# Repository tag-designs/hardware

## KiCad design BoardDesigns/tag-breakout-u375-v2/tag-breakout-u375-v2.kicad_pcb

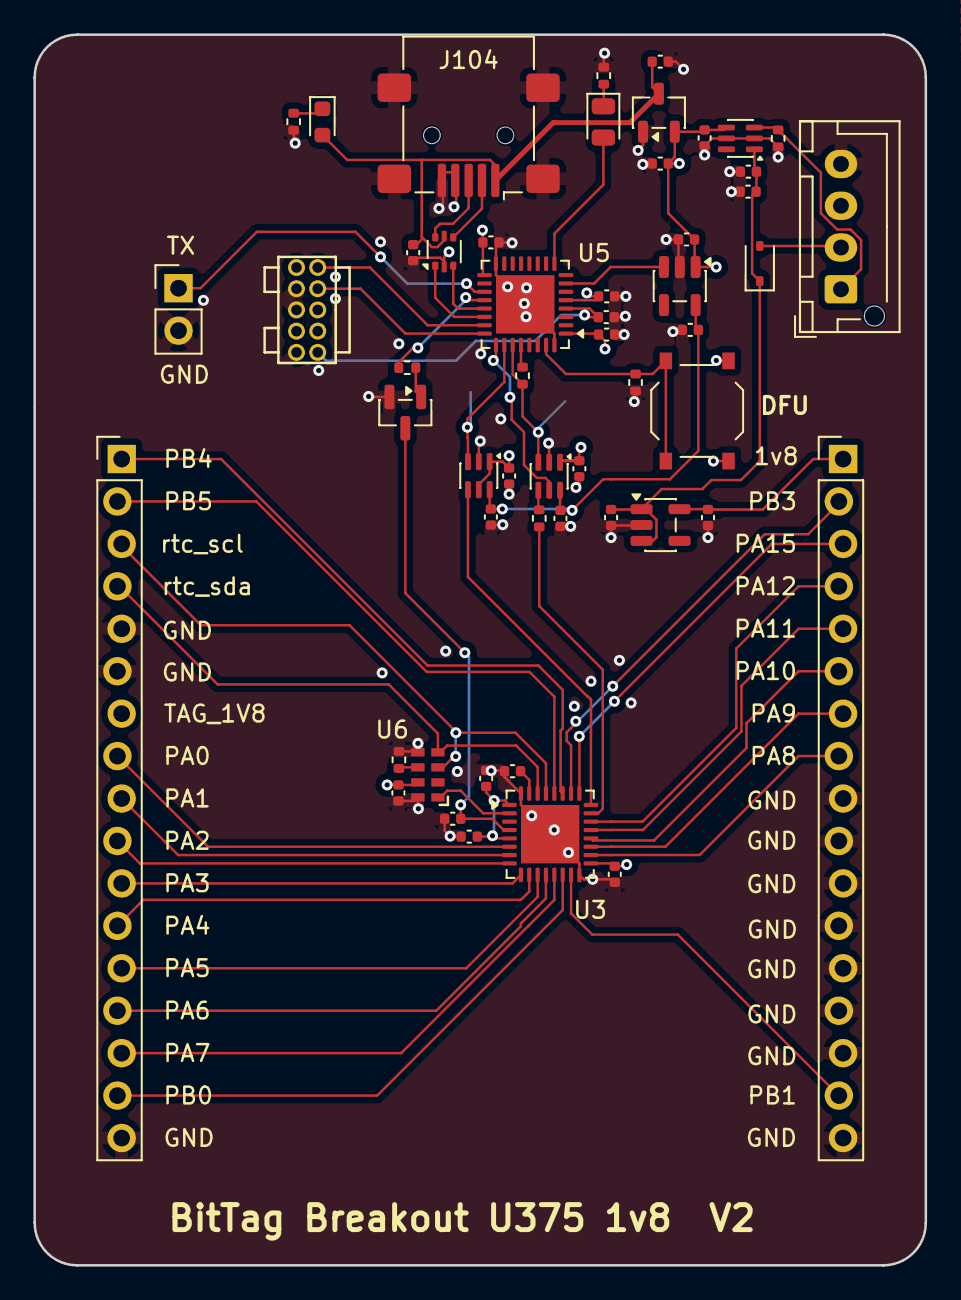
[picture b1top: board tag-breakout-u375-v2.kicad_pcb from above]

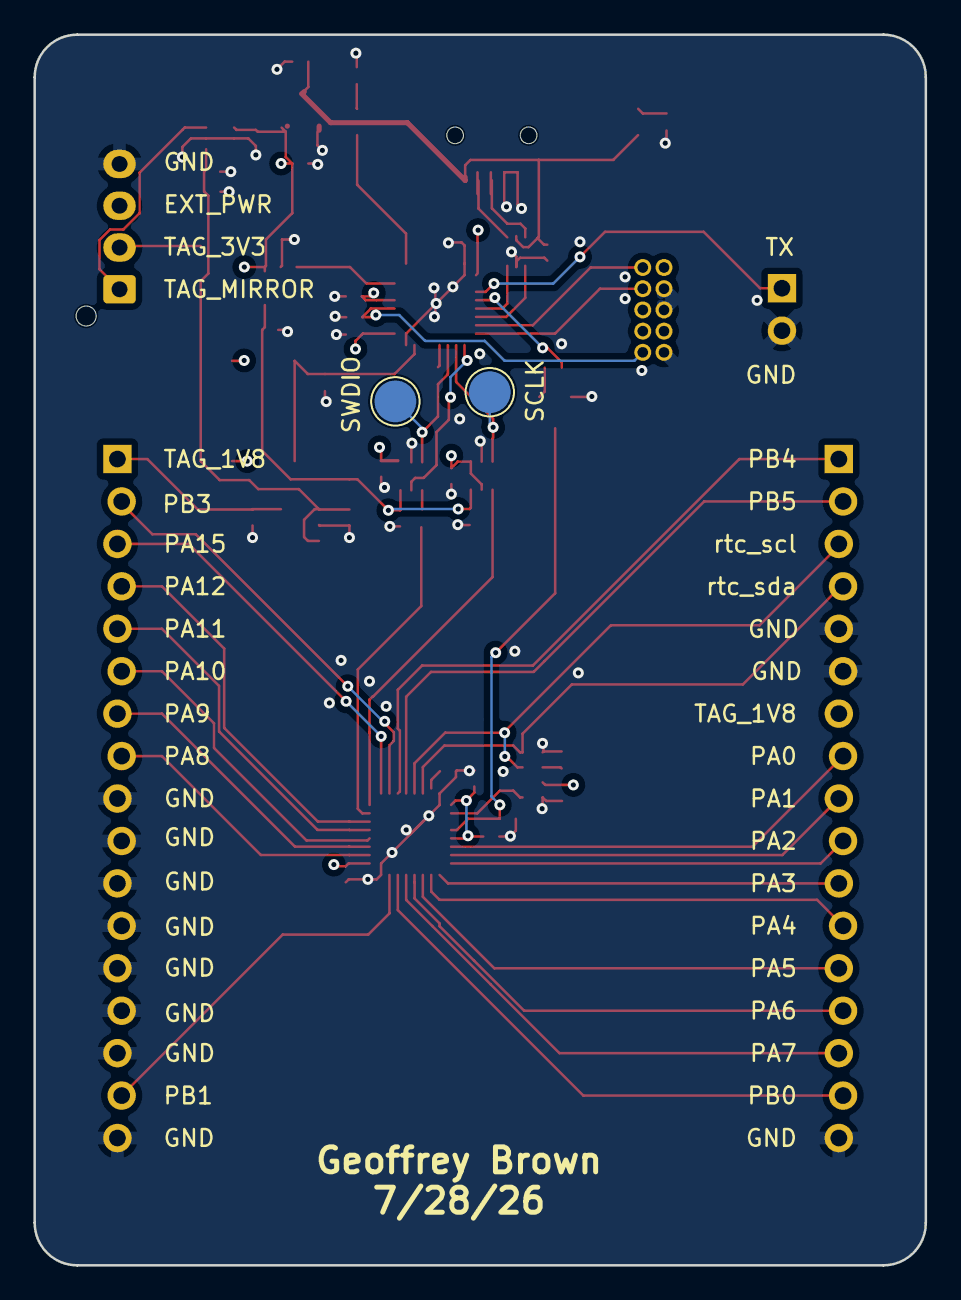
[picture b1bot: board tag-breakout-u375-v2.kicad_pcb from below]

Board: 4 copper layers, 53.3 x 73.7 mm, 55 parts (2 on the bottom side), 55 nets.

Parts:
C1, C12, C104, C105, C106, C108, C112, C114: 1uF; C_0402_1005Metric
C2, C3, C5, C6, C7, C9, C11, C101, C102, C103, C107, C109, C110, C111, C113: 0.1uF; C_0402_1005Metric
C8: 4.7uF; C_0402_1005Metric
D1: LED-GREEN; LED_0805_2012Metric
D4: D_Schottky; D_SOD-323
D105: LED-RED; LED_0603_1608Metric
J1: Conn_01x04_Female; JST_XH_B04B-XH-AM_1x04_P2.50mm_Vertical
J2: Conn_01x02_Male; PinHeader_1x02_P2.54mm_Vertical
J3, J4: Conn_01x17; PinHeader_1x17_P2.54mm_Vertical_Staggered
J102: Conn_02x05_Odd_Even; FTSH-105-01-F-D-K
J104: USB_B_Mini; USB_Mini-B_Lumberg_2486_01_Horizontal
Q1: Q_NPN_BEC; SOT-23
R1, R2, R106: 100; R_0402_1005Metric
R3, R7, R105: 12K; R_0402_1005Metric
R104: 2.2K; R_0402_1005Metric
R107: 200; R_0402_1005Metric
TP1, TP2: TestPoint; TestPoint_Pad_D2.5mm
U1: XC6206; SOT-23-3
U2: SiP32432DR3; SOT-363_SC-70-6
U3: stm32U375; UFQFPN-32-1EP_5x5mm_P0.5mm_EP3.5x3.5mm
U4: USBLC6-2P6; SOT-666
U5: stm32l432; UFQFPN-32-1EP_5x5mm_P0.5mm_EP3.5x3.5mm
U6: RV-3028-C7; RV-8803-C7
U7, U8: SN74LVC1T45DCK; SOT-363_SC-70-6
U10: AP2112K-1.8; SOT-23-5
U11: TPS7A0218PDBVR; SOT-23-5
U105: Tactile Switch; SW_SPST_TS_1187

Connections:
+1V8: C103.1, C105.1, C109.1, U7.6 (VCCB), U8.6 (VCCB), U10.5 (VOUT)
+3V3: C2.1, C11.1, C12.1, C104.1, C107.1, C110.1, C111.1, C112.1, J102.1, U1.2 (VO), U2.4 (IN), U5.1 (VDD), U5.5 (VDDA/VREF+), U5.17 (VDD), U7.1 (VCCA), U7.5 (DIR), U8.1 (VCCA), U10.1 (VIN), U105.2 (B)
/DM: J104.2 (D-), U4.4 (I/O2)
/DP: J104.3 (D+), U4.6 (I/O1)
/LED_GREEN: D1.2 (A), U5.9 (PA3)
/NRST: C101.1, J102.10, U5.4 (~NRST)
/SCLK: J102.4, U5.24 (PA14)
/SWDIO: J102.2, U5.23 (PA13)
/UART_TX: J2.1, U5.19 (PA9)
/USB_DM: U4.3 (I/O2), U5.21 (PA11)
/USB_DP: U4.1 (I/O1), U5.22 (PA12)
/boot0: R105.2, U5.31 (BOOT0), U105.1 (A)
/en1.8v: U5.7 (PA1), U10.3 (EN)
/stm32/NRST: C5.1, Q1.3 (C), U3.4 (~NRST)
/stm32/PA0: J3.8, U3.6 (PA0)
/stm32/PA1: J3.9, U3.7 (PA1)
/stm32/PA2: J3.10, U3.8 (PA2)
/stm32/PA3: J3.11, U3.9 (PA3)
/stm32/PA4: J3.12, U3.10 (PA4)
/stm32/PA5: J3.13, U3.11 (PA5)
/stm32/PA6: J3.14, U3.12 (PA6)
/stm32/PA7: J3.15, U3.13 (PA7)
/stm32/PA8: J4.8, U3.18 (PA8)
/stm32/PA9: J4.7, U3.19 (PA9)
/stm32/PA10: J4.6, U3.20 (PA10)
/stm32/PA11: J4.5, U3.21 (PA11)
/stm32/PA12: J4.4, U3.22 (PA12)
/stm32/PA15: J4.3, U3.25 (PA15)
/stm32/PB0: J3.16, U3.14 (PB0)
/stm32/PB1: J4.16, U3.15 (PB1)
/stm32/PB3: J4.2, U3.26 (PB3)
/stm32/PB4: J3.1, U3.27 (PB4)
/stm32/PB5: J3.2, U3.28 (PB5)
/stm32/VBACK: R3.2, U6.6 (VBACK)
/stm32/clkout: U3.2 (PC14), U6.1 (CLKOUT)
/stm32/rtc_scl: J3.3, U3.29 (PB6), U6.3 (SCL)
/stm32/rtc_sda: J3.4, U3.30 (BOOT0-PB7), U6.4 (SDA)
GND: C1.2, C2.2, C3.2, C5.2, C6.2, C7.2, C8.2, C9.2, C11.2, C12.2, C101.2, C102.2, C103.2, C104.2, C105.2, C106.2, C107.2, C108.2, C109.2, C110.2, C111.2, C112.2, C113.2, C114.2, J1.4, J2.2, J3.5, J3.6, J3.17, J4.9, J4.10, J4.11, J4.12, J4.13, J4.14, J4.15, J4.17, J102.3, J102.5, J102.9, J104.4 (ID), J104.5 (GND), J104.SH (Shield), Q1.2 (E), R1.2, R3.1, R7.2, R105.1, R107.2, U1.1 (GND), U2.2 (GND), U2.5 (GND), U3.16 (VSS), U3.32 (VSS), U3.33 (GND), U4.2 (GND), U5.16 (VSS), U5.32 (VSS), U5.33 (GND), U6.5 (GND), U6.8 (EVI), U7.2 (GND), U8.2 (GND), U10.2 (GND), U11.2 (GND)
unnamed: D1.1 (K), R1.1
unnamed: D105.1 (K), R107.1
unnamed: C8.1, U3.31 (VCAP)
unnamed: R104.1, U5.20 (PA10)
unnamed: U5.25 (PA15), U8.5 (DIR)
unnamed: TP2.1 (1_1), U5.26 (PB3), U7.3 (A)
unnamed: R2.2, TP1.1 (1_1), U5.27 (PB4), U8.3 (A)
unnamed: R2.1, U5.28 (PB5)
unnamed: R106.1, U8.4 (B)
PWR_IN: D4.2 (A), J1.2
PWR_IN_MIRROR: J1.1, R7.1, U2.3 (~ON)
TAG_1V8: C3.1, C6.1, C7.1, C9.1, C106.1, J3.7, J4.1, U3.1 (VDD), U3.5 (VDDA/VREF+), U3.17 (VDD), U6.7 (VDD), U11.5 (OUT)
TAG_3V3: C108.1, C113.1, C114.1, D4.1 (K), U2.1 (OUT), U11.1 (IN), U11.3 (EN)
TAG_RESET: Q1.1 (B), R104.2
TAG_SCK: U3.24 (PA14), U7.4 (B)
TAG_SWDIO: R106.2, U3.23 (PA13)
VUSB: C1.1, C102.1, D105.2 (A), J104.1 (VBUS), U1.3 (VI), U4.5 (VBUS)

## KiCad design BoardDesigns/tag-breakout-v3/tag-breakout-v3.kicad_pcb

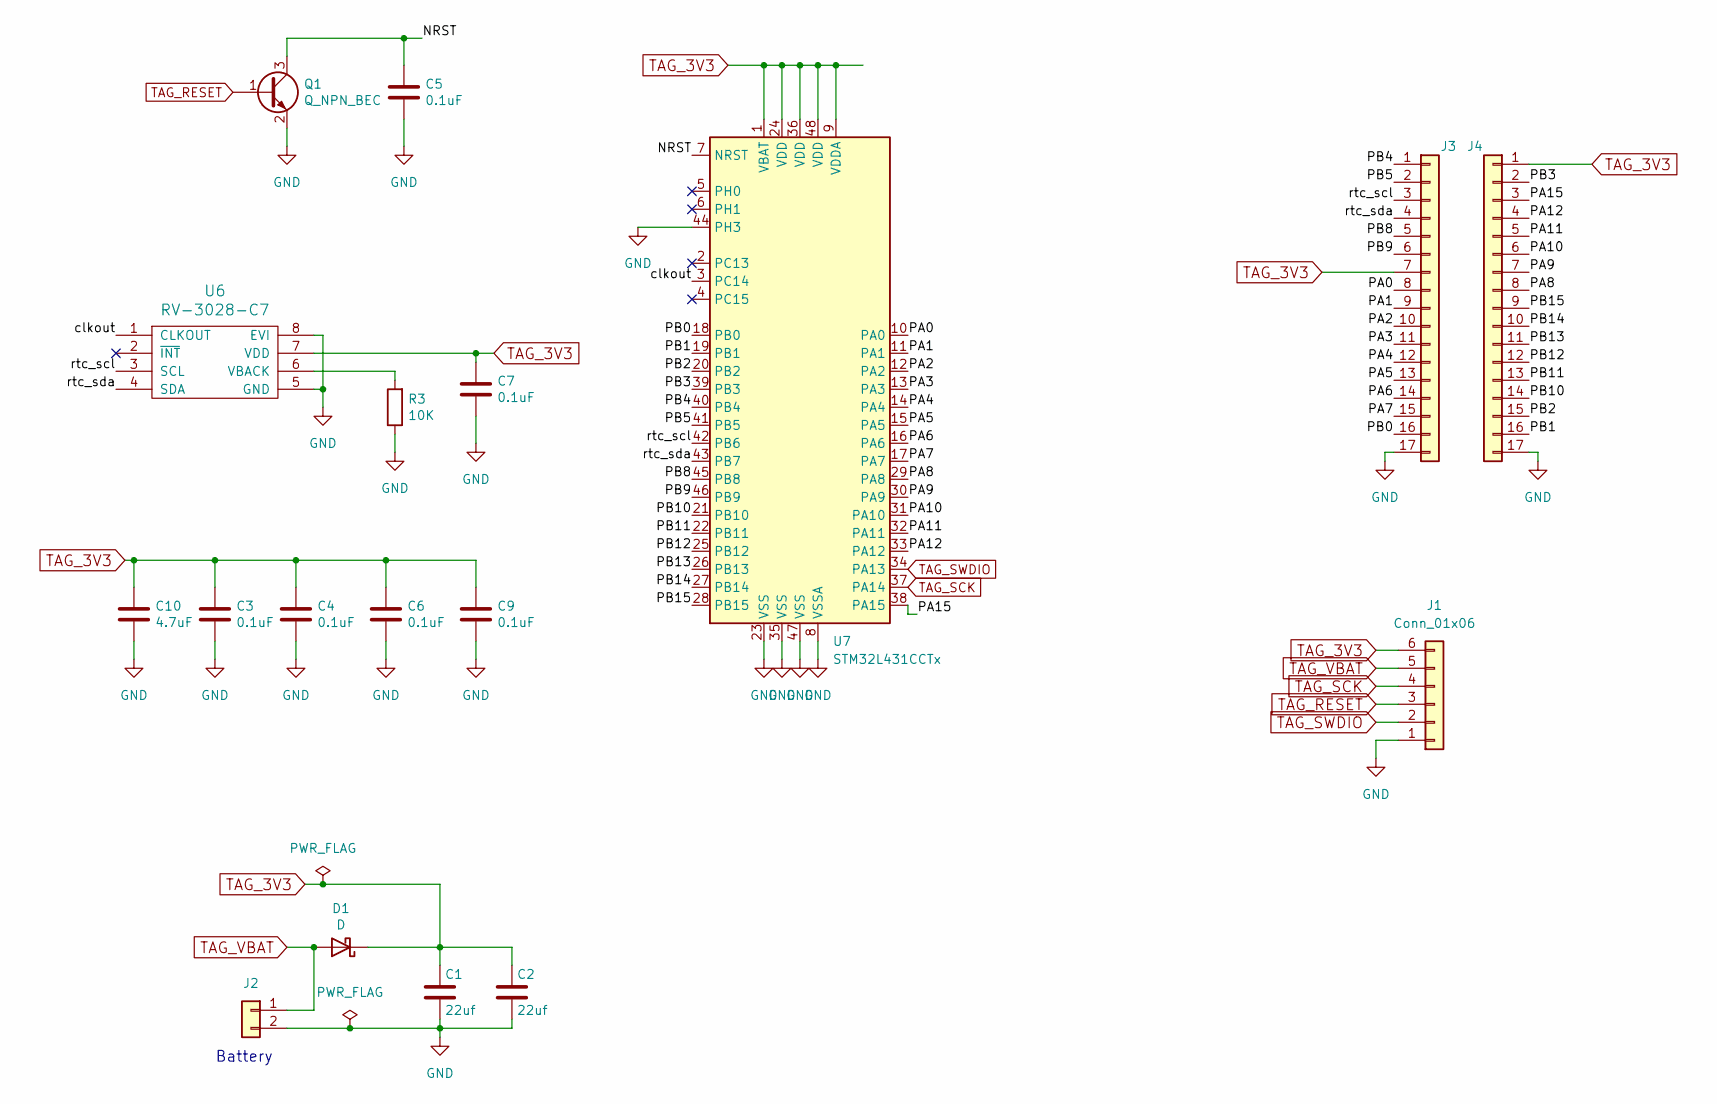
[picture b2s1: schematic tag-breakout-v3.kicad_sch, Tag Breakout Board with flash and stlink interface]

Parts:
C1, C2: 22uf; C_0402_1005Metric; MPN 04026D226MAT2A
C3, C4, C5, C6, C7, C9: 0.1uF; C_0603_1608Metric; LCSC C14663
C10: 4.7uF; C_0603_1608Metric; LCSC C19666
D1: D; D_0402_1005Metric; MPN CDBQC0130L-HF
J1: Conn_01x06; CONN_B6B-ZR_JST
J2: CONN_01X02; PinHeader_1x02_P2.54mm_Vertical
J3, J4: Conn_01x17; PinSocket_1x17_P2.54mm_Vertical
Q1: Q_NPN_BEC; SOT-23; LCSC C20527
R3: 10K; R_0603_1608Metric; LCSC C25804
U6: RV-3028-C7; RV-8803-C7
U7: STM32L431CCTx; LQFP-48_7x7mm_P0.5mm; JLC C486681

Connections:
/NRST: C5.1, Q1.3 (C), U7.7 (NRST)
/PA0: J3.8, U7.10 (PA0)
/PA1: J3.9, U7.11 (PA1)
/PA2: J3.10, U7.12 (PA2)
/PA3: J3.11, U7.13 (PA3)
/PA4: J3.12, U7.14 (PA4)
/PA5: J3.13, U7.15 (PA5)
/PA6: J3.14, U7.16 (PA6)
/PA7: J3.15, U7.17 (PA7)
/PA8: J4.8, U7.29 (PA8)
/PA9: J4.7, U7.30 (PA9)
/PA10: J4.6, U7.31 (PA10)
/PA11: J4.5, U7.32 (PA11)
/PA12: J4.4, U7.33 (PA12)
/PA15: J4.3, U7.38 (PA15)
/PB0: J3.16, U7.18 (PB0)
/PB1: J4.16, U7.19 (PB1)
/PB2: J4.15, U7.20 (PB2)
/PB3: J4.2, U7.39 (PB3)
/PB4: J3.1, U7.40 (PB4)
/PB5: J3.2, U7.41 (PB5)
/PB8: J3.5, U7.45 (PB8)
/PB9: J3.6, U7.46 (PB9)
/PB10: J4.14, U7.21 (PB10)
/PB11: J4.13, U7.22 (PB11)
/PB12: J4.12, U7.25 (PB12)
/PB13: J4.11, U7.26 (PB13)
/PB14: J4.10, U7.27 (PB14)
/PB15: J4.9, U7.28 (PB15)
/clkout: U6.1 (CLKOUT), U7.3 (PC14)
/rtc_scl: J3.3, U6.3 (SCL), U7.42 (PB6)
/rtc_sda: J3.4, U6.4 (SDA), U7.43 (PB7)
GND: C1.2, C2.2, C3.2, C4.2, C5.2, C6.2, C7.2, C9.2, C10.2, J1.1, J2.2, J3.17, J4.17, Q1.2 (E), R3.1, U6.5 (GND), U6.8 (EVI), U7.8 (VSSA), U7.23 (VSS), U7.35 (VSS), U7.44 (PH3), U7.47 (VSS)
unnamed: R3.2, U6.6 (VBACK)
TAG_3V3: C1.1, C2.1, C3.1, C4.1, C6.1, C7.1, C9.1, C10.1, D1.1 (K), J1.6, J3.7, J4.1, U6.7 (VDD), U7.1 (VBAT), U7.9 (VDDA), U7.24 (VDD), U7.36 (VDD), U7.48 (VDD)
TAG_RESET: J1.3, Q1.1 (B)
TAG_SCK: J1.4, U7.37 (PA14)
TAG_SWDIO: J1.2, U7.34 (PA13)
TAG_VBAT: D1.2 (A), J1.5, J2.1

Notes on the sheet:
Battery

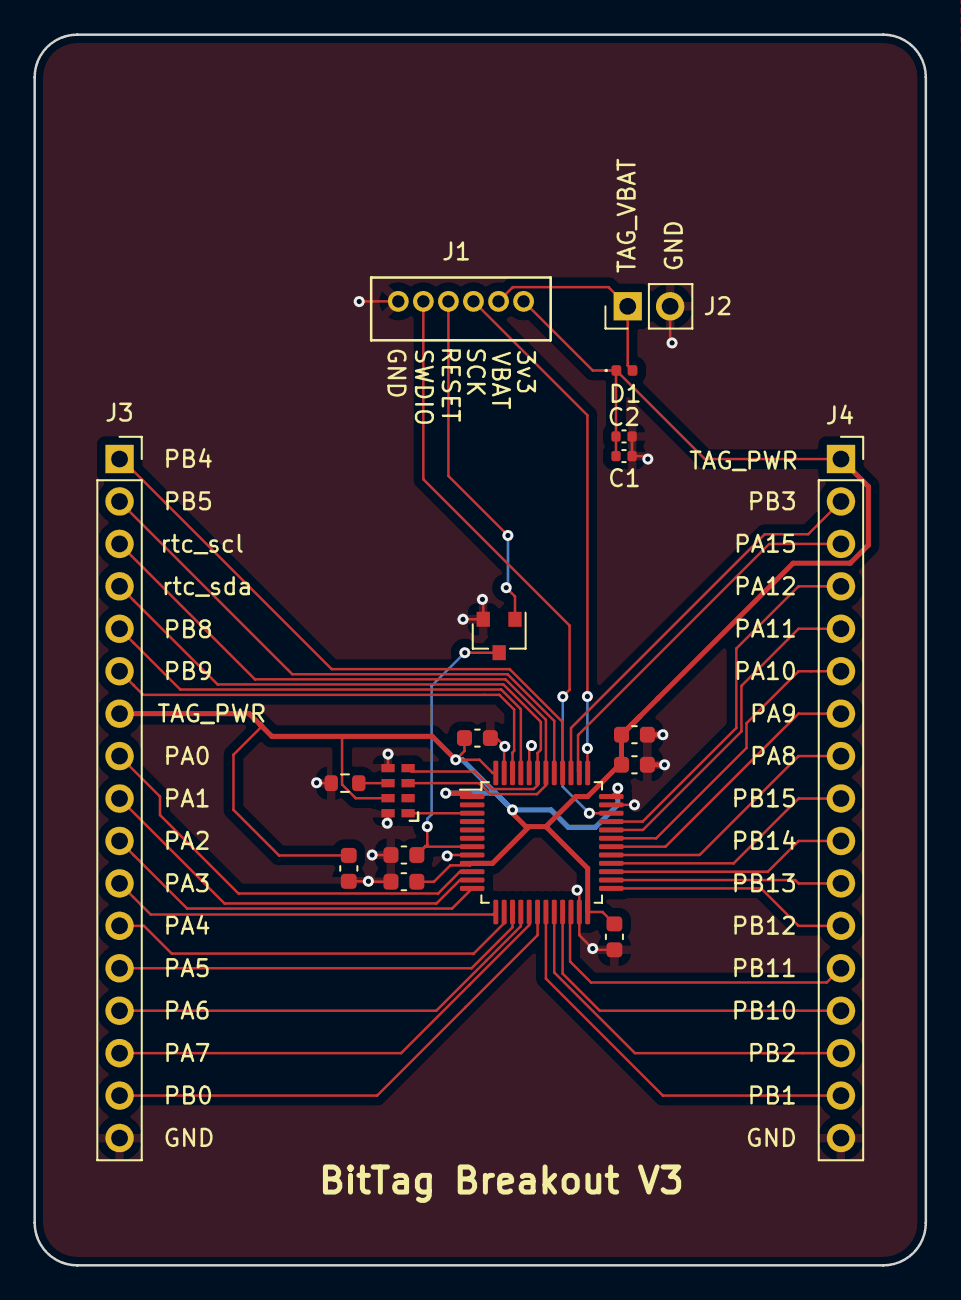
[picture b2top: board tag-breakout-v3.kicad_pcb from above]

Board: 2 copper layers, 53.3 x 73.7 mm, 18 parts (0 on the bottom side), 39 nets.

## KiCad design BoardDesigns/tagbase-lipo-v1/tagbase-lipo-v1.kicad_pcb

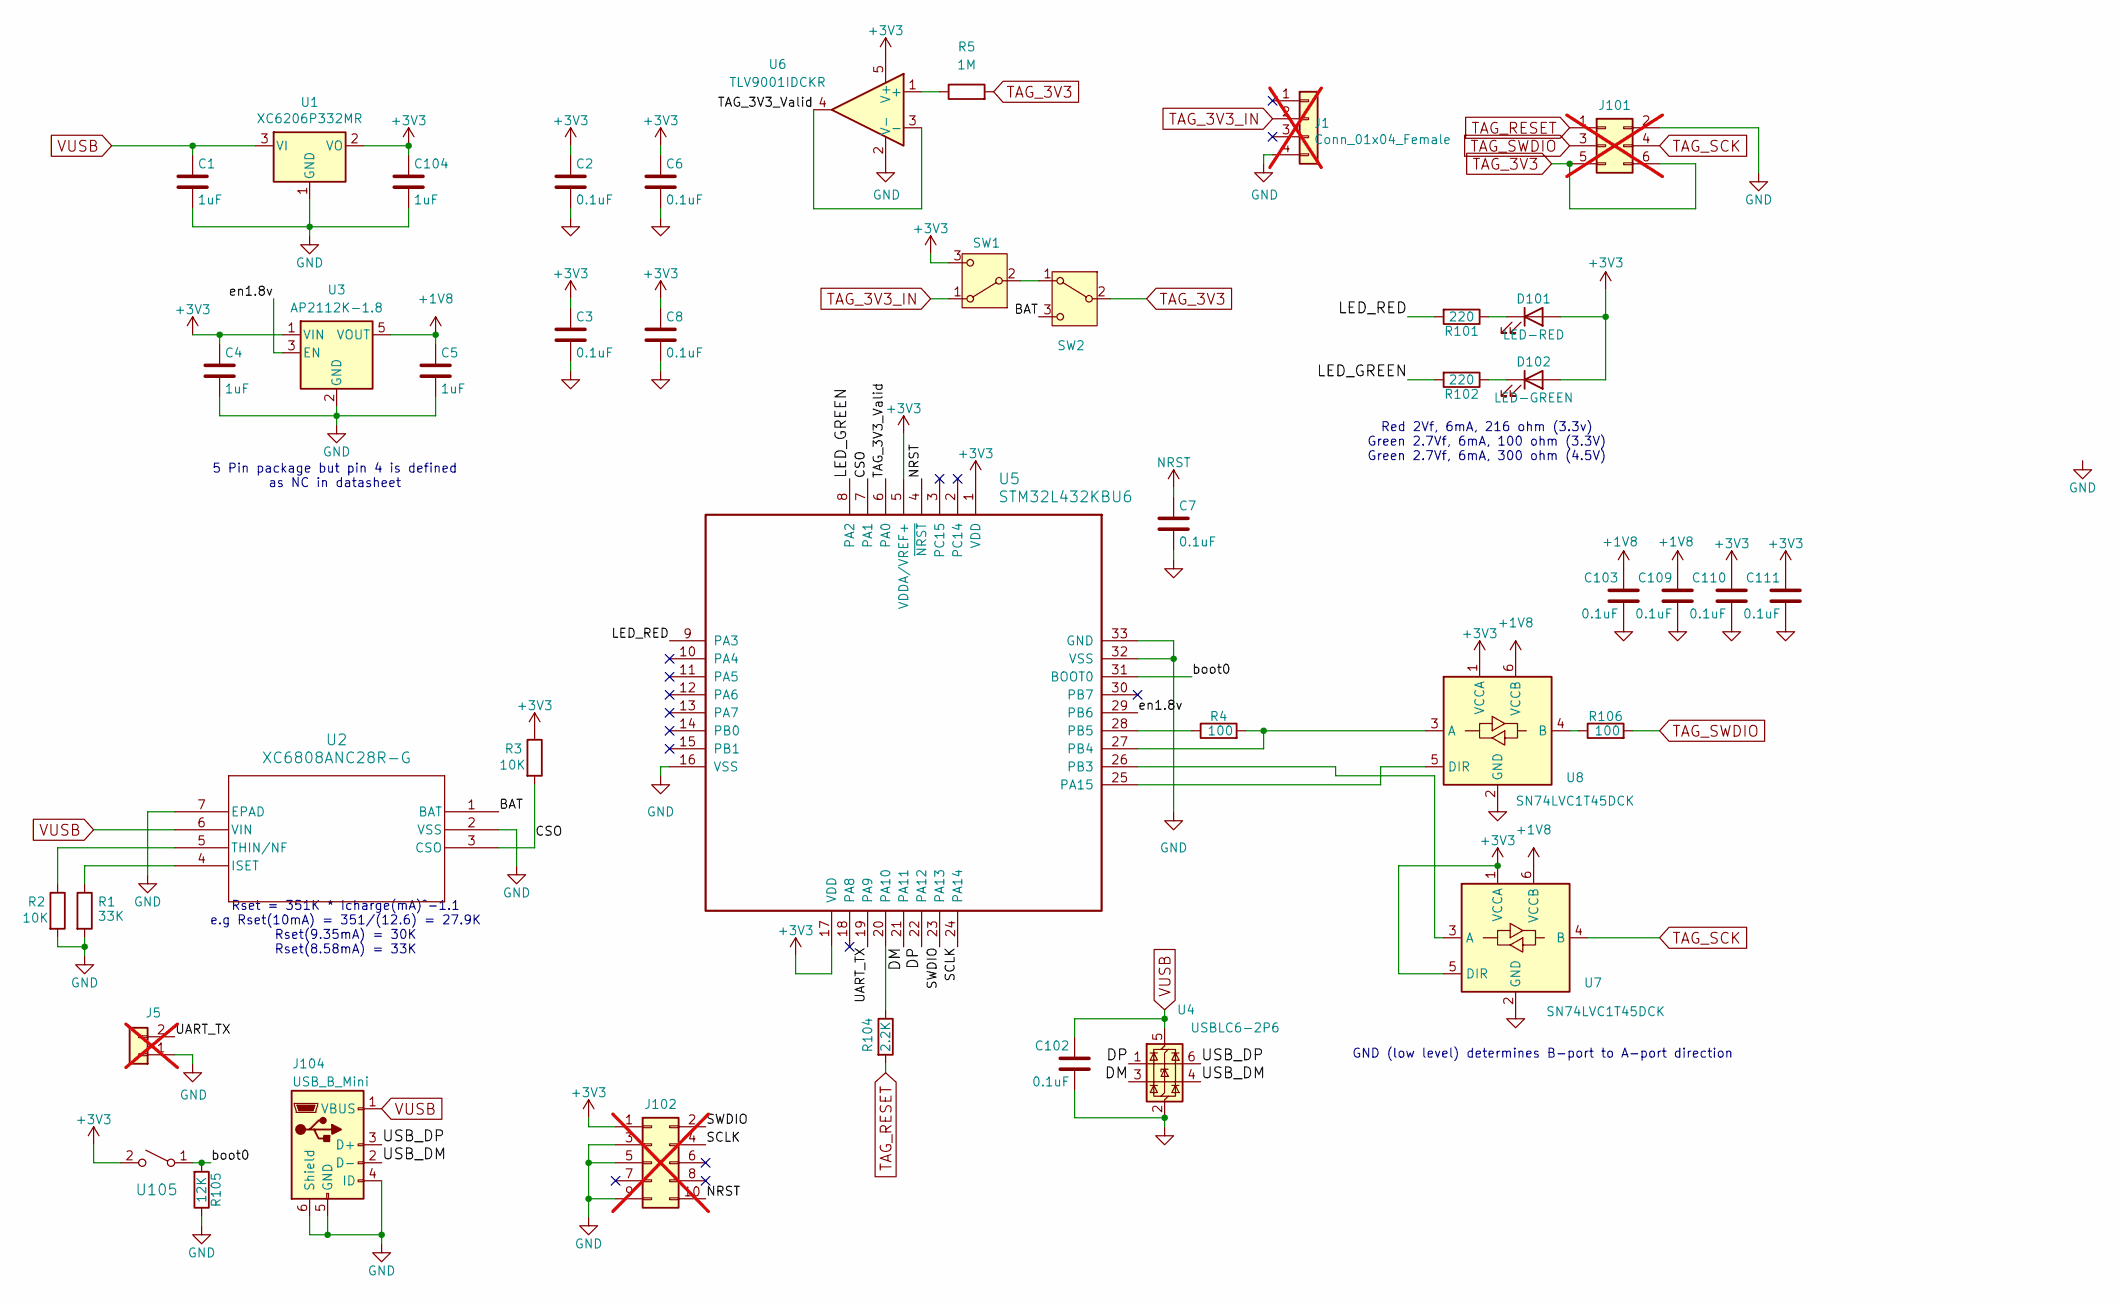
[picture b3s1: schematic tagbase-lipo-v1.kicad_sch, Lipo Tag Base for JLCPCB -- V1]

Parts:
C1, C4, C5, C104: 1uF; C_0402_1005Metric; MPN CL05A105KA5NQNC; LCSC C52923
C2, C3, C6, C7, C8, C102, C103, C109, C110, C111: 0.1uF; C_0402_1005Metric; MPN CL05B104KO5NNNC; LCSC C1525
D101: LED-RED; D_0805_2012Metric; MPN NCD0805R1; LCSC C84256
D102: LED-GREEN; D_0805_2012Metric; MPN KT-0805G; LCSC C2297
J1: Conn_01x04_Female; JST_XH_B04B-XH-AM_1x04_P2.50mm_Vertical; not fitted
J5: Conn_01x02; PinHeader_1x02_P2.54mm_Vertical; not fitted
J101: Conn_02x03_Odd_Even; 6pin_tagpoints_double_screws; not fitted
J102: Conn_02x05_Odd_Even; FTSH-105-01-F-D-K; not fitted
J104: USB_B_Mini; USB_Mini-B; MPN MINI 5PTP; LCSC C2681563
R1: 33K; R_0402_1005Metric; MPN 0402WGF3302TCE; LCSC C25779
R2, R3: 10K; R_0402_1005Metric; MPN 0402WGF1002TCE; LCSC C25744
R4, R106: 100; R_0402_1005Metric; MPN 0402WGF1000TCE; LCSC C25076
R5: 1M; R_0402_1005Metric; MPN 0402WGF1004TCE; LCSC C26083
R101, R102: 220; R_0603_1608Metric; MPN 0603WAF1000T5E; LCSC C22775
R104: 2.2K; R_0402_1005Metric; MPN 0402WGF2201TCE; LCSC C25879
R105: 12K; R_0402_1005Metric; MPN 0402WGF1202TCE; LCSC C25752
SW1, SW2: SW_SPDT; CJS-1200B_NDC; MPN CJS-1200B2; LCSC C35817163
U1: XC6206P332MR; SOT-23-3; MPN XC6206P332MR; LCSC C5446
U2: XC6808ANC28R-G; xc6808; MPN XC6808A4C28R-G; LCSC C3682502
U3: AP2112K-1.8; SOT-23-5; MPN AP2112K-1.8TRG1(MS); LCSC C22365428
U4: USBLC6-2P6; SOT-666; MPN USBLC6-2P6; LCSC C15999
U5: STM32L432KBU6; UFQFPN-32-1EP_5x5mm_P0.5mm_EP3.5x3.5mm; MPN STM32L432KBU6; LCSC C94784
U6: TLV9001IDCKR; SOT-353_SC-70-5; MPN TLV9001IDCKR; LCSC C398362
U7, U8: SN74LVC1T45DCK; SOT-363_SC-70-6; MPN SN74LVC1T45DCKR; LCSC C9382
U105: Tactile Switch; SW_SPST_TS_1187; MPN TS-1187A-C-E-B; LCSC C318889

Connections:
+1V8: C5.1, C103.1, C109.1, U3.5 (VOUT), U7.6 (VCCB), U8.6 (VCCB)
+3V3: C2.1, C3.1, C4.1, C6.1, C8.1, C104.1, C110.1, C111.1, D101.2 (A), D102.2 (A), J102.1, R3.1, SW1.3 (C), U1.2 (VO), U3.1 (VIN), U5.1 (VDD), U5.5 (VDDA/VREF+), U5.17 (VDD), U6.5 (V+), U7.1 (VCCA), U7.5 (DIR), U8.1 (VCCA), U105.2 (B)
/BAT: SW2.3 (C), U2.1 (BAT); also elsewhere on the board
/CSO: R3.2, U2.3 (CSO), U5.7 (PA1)
/DM: U4.3 (I/O2), U5.21 (USB_DM)
/DP: U4.1 (I/O1), U5.22 (USB_DP)
/LED_GREEN: R102.2, U5.8 (PA2)
/LED_RED: R101.2, U5.9 (PA3)
/SCLK: J102.4, U5.24 (PA14)
/SWDIO: J102.2, U5.23 (PA13)
/UART_TX: J5.2, U5.19 (USART1_TX)
/USB_DM: J104.2 (D-), U4.4 (I/O2)
/USB_DP: J104.3 (D+), U4.6 (I/O1)
/boot0: R105.2, U5.31 (BOOT0), U105.1 (A)
/en1.8v: U3.3 (EN), U5.29 (PB6)
GND: C1.2, C2.2, C3.2, C4.2, C5.2, C6.2, C7.2, C8.2, C102.2, C103.2, C104.2, C109.2, C110.2, C111.2, J1.4, J5.1, J101.2, J102.3, J102.5, J102.9, J104.4 (ID), J104.5 (GND), J104.6 (Shield), R1.2, R2.2, R105.1, U1.1 (GND), U2.2 (VSS), U2.7 (EPAD), U3.2 (GND), U4.2 (GND), U5.16 (VSS), U5.32 (VSS), U5.33 (GND), U6.2 (V-), U7.2 (GND), U8.2 (GND); also elsewhere on the board
NRST: C7.1, J102.10, U5.4 (~NRST)
unnamed: D101.1 (K), R101.1
unnamed: D102.1 (K), R102.1
unnamed: SW1.2 (B), SW2.1 (A)
unnamed: R1.1, U2.4 (ISET)
unnamed: R2.1, U2.5 (THIN/NF)
unnamed: R104.1, U5.20 (PA10)
unnamed: U5.25 (PA15), U8.5 (DIR)
unnamed: U5.26 (SPI1_SCK), U7.3 (A)
unnamed: R4.2, U5.27 (SPI1_MISO), U8.3 (A)
unnamed: R4.1, U5.28 (SPI1_MOSI)
unnamed: R5.1, U6.1 (+)
unnamed: R106.1, U8.4 (B)
TAG_3V3: J101.5, J101.6, R5.2, SW2.2 (B)
TAG_3V3_IN: J1.2, SW1.1 (A)
TAG_RESET: J101.1, R104.2
TAG_SCK: J101.4, U7.4 (B)
TAG_SWDIO: J101.3, R106.2
VUSB: C1.1, C102.1, J104.1 (VBUS), U1.3 (VI), U2.6 (VIN), U4.5 (VBUS); also elsewhere on the board

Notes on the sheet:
Rset = 351K * Icharge(mA)^-1.1 e.g Rset(10mA) = 351/(12.6) = 27.9K Rset(9.35mA) = 30K Rset(8.58mA) = 33K
5 Pin package but pin 4 is defined as NC in datasheet
GND (low level) determines B-port to A-port direction
Red 2Vf, 6mA, 216 ohm (3.3v) Green 2.7Vf, 6mA, 100 ohm (3.3V) Green 2.7Vf, 6mA, 300 ohm (4.5V)

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
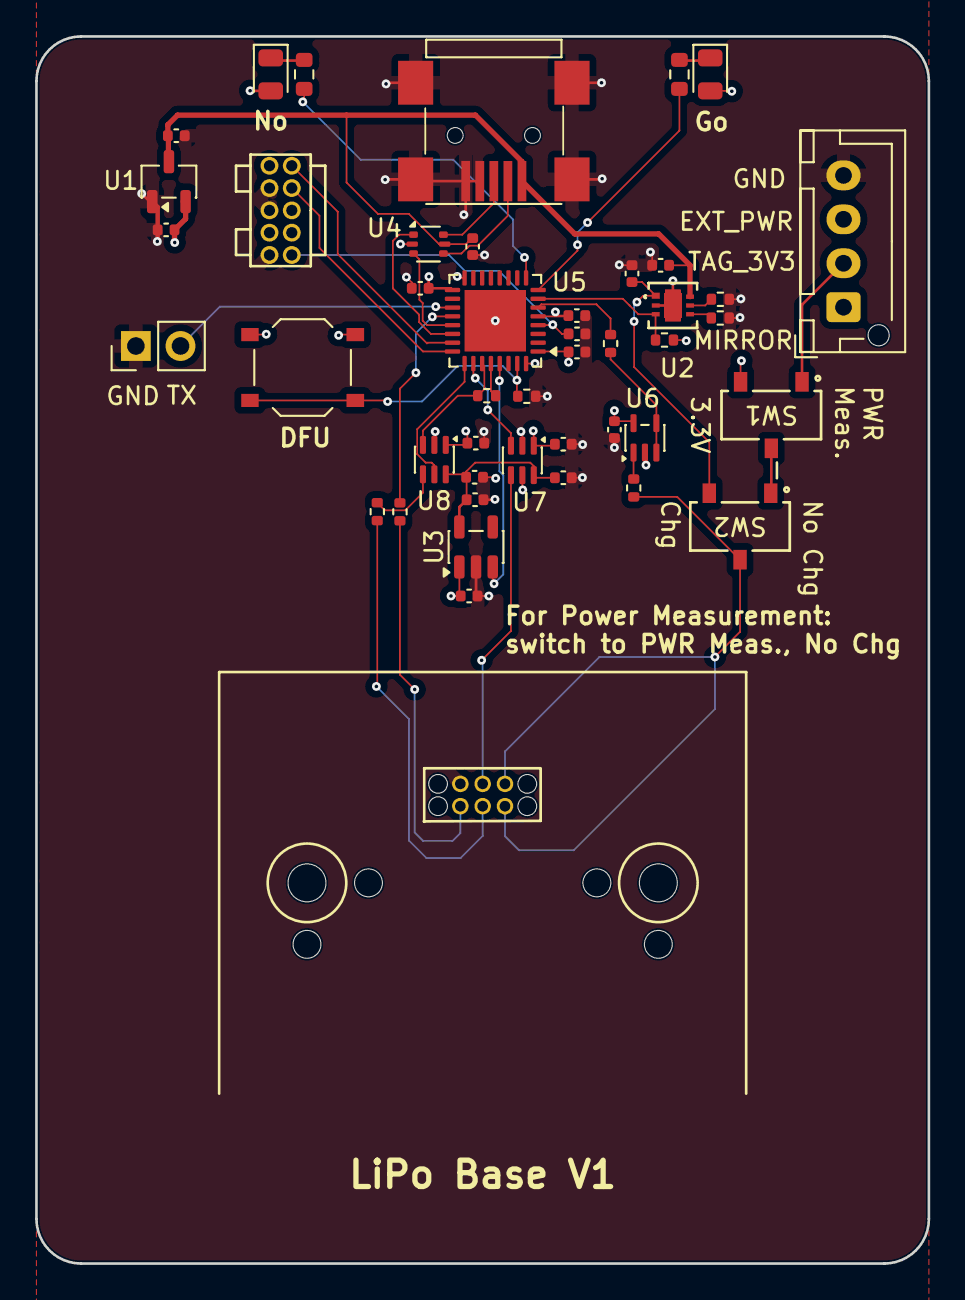
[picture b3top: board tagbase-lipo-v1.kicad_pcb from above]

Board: 4 copper layers, 50.8 x 69.9 mm, 45 parts (0 on the bottom side), 37 nets.

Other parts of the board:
C9, C10: 1uF; C_0402_1005Metric
R107: 2.2K; R_0402_1005Metric

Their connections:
/BAT: C9.1; also elsewhere on the board
GND: C9.2, C10.2; also elsewhere on the board
VUSB: C10.1; also elsewhere on the board

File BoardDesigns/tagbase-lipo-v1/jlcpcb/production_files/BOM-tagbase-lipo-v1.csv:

Comment,Designator,Footprint,LCSC,Quantity
0.1uF,"C102,C103,C109,C110,C111,C2,C3,C6,C7,C8",C_0402_1005Metric,C1525,10
100,"R106,R4",R_0402_1005Metric,C25076,2
10K,"R2,R3",R_0402_1005Metric,C25744,2
12K,R105,R_0402_1005Metric,C25752,1
1M,R5,R_0402_1005Metric,C26083,1
1uF,"C1,C10,C104,C4,C5,C9",C_0402_1005Metric,C52923,6
2.2K,"R104,R107",R_0402_1005Metric,C25879,2
220,"R101,R102",R_0603_1608Metric,C22775,2
33K,R1,R_0402_1005Metric,C25779,1
AP2112K-1.8,U3,SOT-23-5,C22365428,1
LED-GREEN,D102,D_0805_2012Metric,C2297,1
LED-RED,D101,D_0805_2012Metric,C84256,1
SN74LVC1T45DCK,"U7,U8",SOT-363_SC-70-6,C9382,2
STM32L432KBU6,U5,UFQFPN-32-1EP_5x5mm_P0.5mm_EP3.5x3.5mm,C94784,1
SW_SPDT,"SW1,SW2",CJS-1200B_NDC,C35817163,2
TLV9001IDCKR,U6,SOT-353_SC-70-5,C398362,1
Tactile Switch,U105,SW_SPST_TS_1187,C318889,1
USBLC6-2P6,U4,SOT-666,C15999,1
USB_B_Mini,J104,USB_Mini-B,C2681563,1
XC6206P332MR,U1,SOT-23-3,C5446,1
XC6808A4C28R-G,U2,xc6808,C3682502,1

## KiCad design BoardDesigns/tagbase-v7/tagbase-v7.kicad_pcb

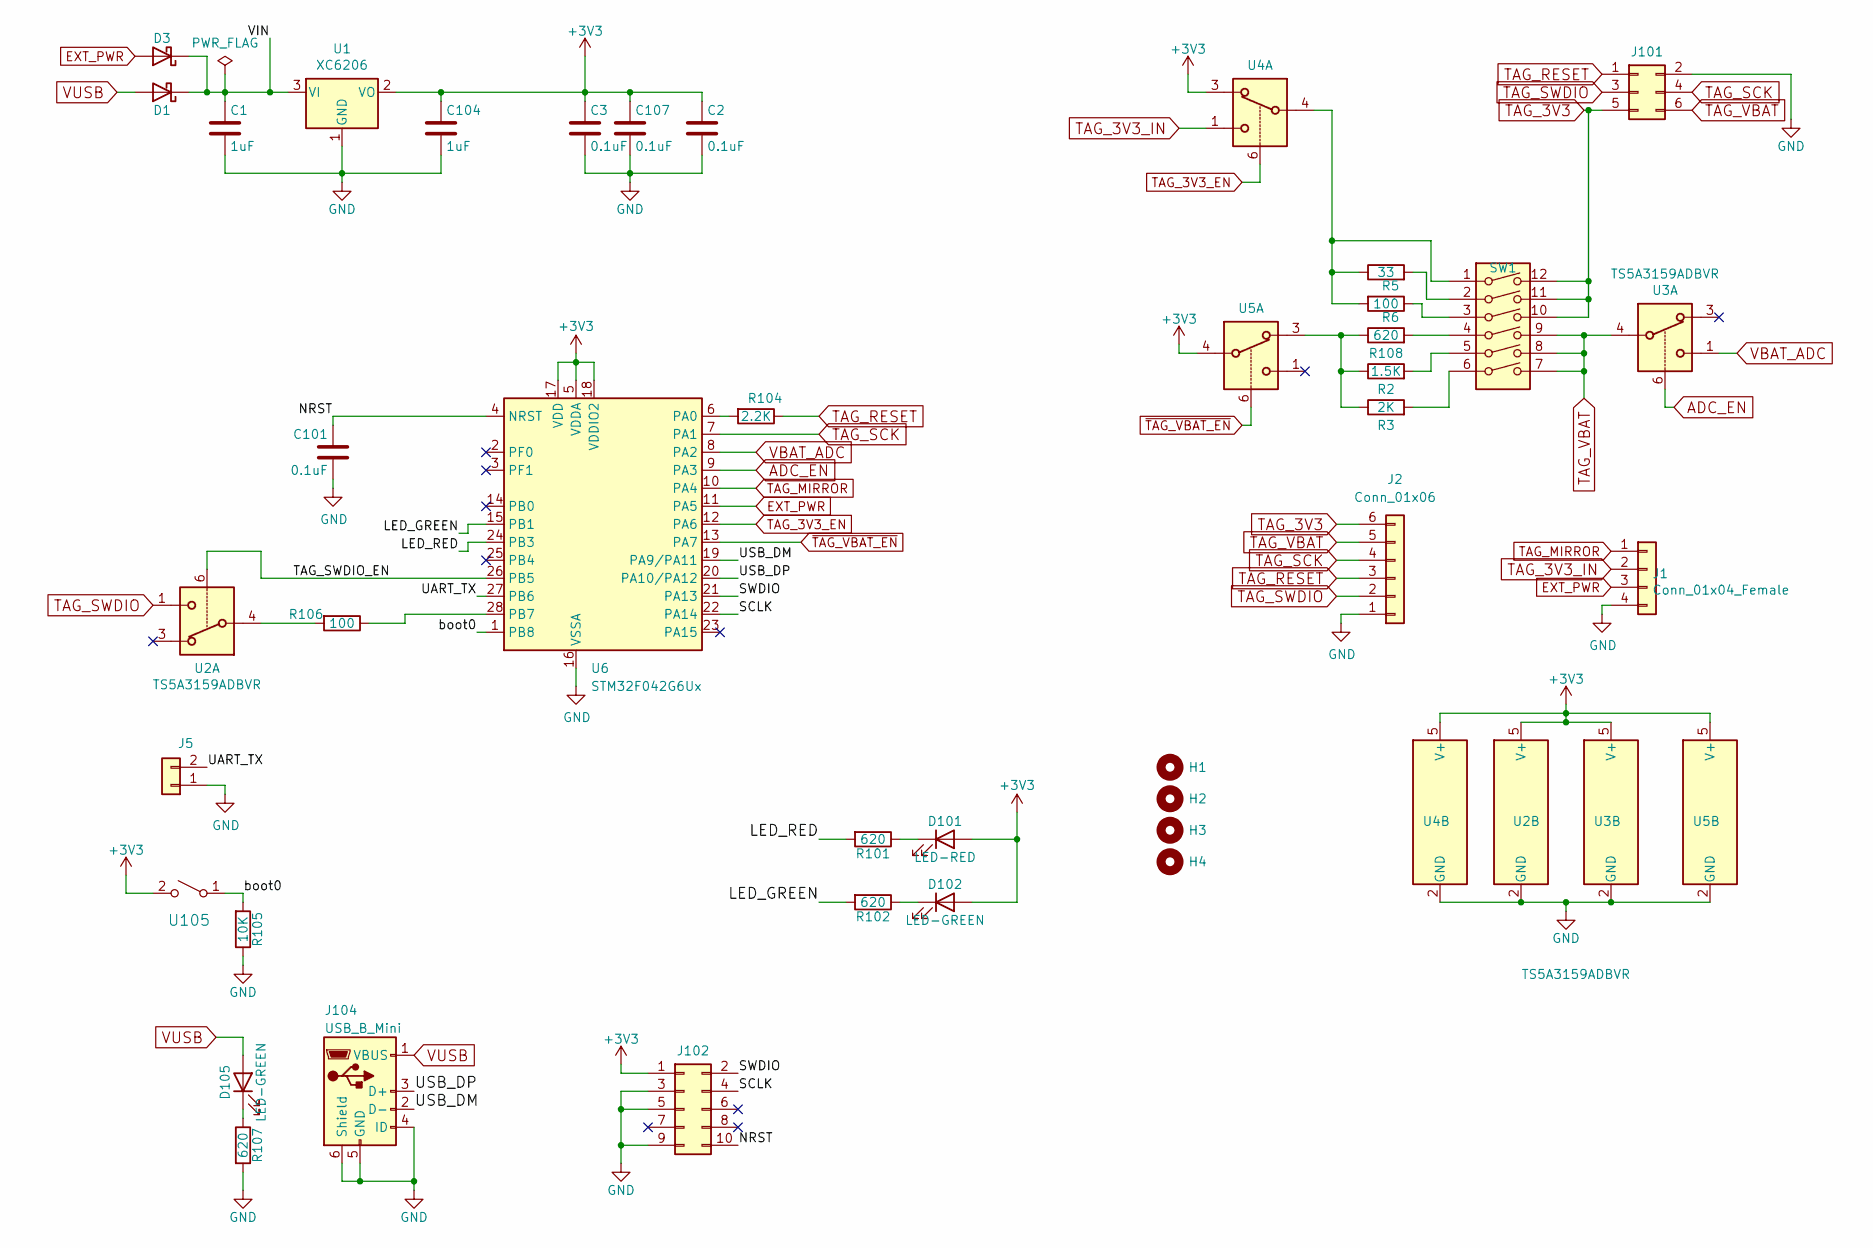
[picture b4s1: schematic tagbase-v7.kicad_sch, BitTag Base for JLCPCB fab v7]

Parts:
C1, C104: 1uF; C_0603_1608Metric; MPN CL10A105KB8NNNC; LCSC C15849
C2, C3, C101, C107: 0.1uF; C_0603_1608Metric; MPN CC0603KRX7R9BB104; LCSC C14663
D1, D3: DIODE; D_SOD-123; MPN B5819W; LCSC C8598
D101: LED-RED; LED_0603_1608Metric; MPN KT-0603R; LCSC C2286
D102, D105: LED-GREEN; LED_0603_1608Metric; MPN 19-217/GHC-YR1S2/3T; LCSC C72043
H1, H2, H3, H4: MountingHole; MountingHole_2.5mm
J1: Conn_01x04_Female; JST_XH_B04B-XH-AM_1x04_P2.50mm_Vertical
J2: Conn_01x06; JST_B6B-ZR(LF)(SN)
J5: Conn_01x02; PinHeader_1x02_P2.54mm_Vertical
J101: Conn_02x03_Odd_Even; 6pin_tagpoints_new_offset
J102: Conn_02x05_Odd_Even; FTSH-105-01-F-D-K
J104: USB_B_Mini; USB_Mini-B; MPN MINI 5PTP; LCSC C2681563
R2: 1.5K; R_0603_1608Metric; MPN 0603WAF1501T5E; LCSC C22843
R3: 2K; R_0603_1608Metric; MPN 0603WAF2001T5E; LCSC C22975
R5: 33; R_0603_1608Metric; MPN 0603WAF330JT5E; LCSC C23140
R6, R106: 100; R_0603_1608Metric; MPN 0603WAF1000T5E; LCSC C22775
R101, R102, R107, R108: 620; R_0603_1608Metric; MPN 0603WAF6200T5E; LCSC C23220
R104: 2.2K; R_0603_1608Metric; MPN 0603WAF1002T5E; LCSC C4190
R105: 10K; R_0603_1608Metric; MPN 0603WAF1002T5E; LCSC C25804
SW1: SW_DIP_x04; SW_DIP_SPSTx06_Slide_KingTek_DSHP06TS_W7.62mm_P1.27mm; MPN DSHP06TSGER; LCSC C3293146
U1: XC6206; SOT-23-3; MPN XC6206P332MR; LCSC C5446
U2, U3, U4, U5: TS5A3159ADBVR; SOT-23-6; MPN TS5A3159ADBVR; LCSC C128405
U6: STM32F042G6Ux; QFN-28_4x4mm_P0.5mm; MPN STM32F042G6U6; LCSC C961597
U105: Tactile Switch; SW_SPST_TS_1187; MPN TS-1187A-C-E-B; LCSC C318889

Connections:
+3V3: C2.1, C3.1, C104.1, C107.1, D101.2 (A), D102.2 (A), J102.1, U1.2 (VO), U2.5 (V+), U3.5 (V+), U4.3, U4.5 (V+), U5.4, U5.5 (V+), U6.5 (VDDA), U6.17 (VDD), U6.18 (VDDIO2), U105.2 (B)
/LED_GREEN: R102.2, U6.15 (PB1)
/LED_RED: R101.2, U6.24 (PB3)
/NRST: C101.1, J102.10, U6.4 (NRST)
/SCLK: J102.4, U6.22 (PA14)
/SWDIO: J102.2, U6.21 (PA13)
/TAG_SWDIO_EN: U2.6, U6.26 (PB5)
/UART_TX: J5.2, U6.27 (PB6)
/USB_DM: J104.2 (D-), U6.19 (PA9/PA11)
/USB_DP: J104.3 (D+), U6.20 (PA10/PA12)
/VIN: C1.1, D1.1 (K), D3.1 (K), U1.3 (VI)
/boot0: R105.2, U6.1 (PB8), U105.1 (A)
ADC_EN: U3.6, U6.9 (PA3)
EXT_PWR: D3.2 (A), J1.3, U6.11 (PA5)
GND: C1.2, C2.2, C3.2, C101.2, C104.2, C107.2, J1.4, J2.1, J5.1, J101.2, J102.3, J102.5, J102.9, J104.4 (ID), J104.5 (GND), J104.6 (Shield), R105.1, R107.2, U1.1 (GND), U2.2 (GND), U3.2 (GND), U4.2 (GND), U5.2 (GND), U6.16 (VSSA)
unnamed: D101.1 (K), R101.1
unnamed: D102.1 (K), R102.1
unnamed: D105.1 (K), R107.1
unnamed: R2.2, SW1.5
unnamed: R3.2, SW1.6
unnamed: R5.1, R6.2, SW1.1, U4.4
unnamed: R5.2, SW1.2
unnamed: R6.1, SW1.3
unnamed: R104.2, U6.6 (PA0)
unnamed: R106.1, U6.28 (PB7)
unnamed: R106.2, U2.4
unnamed: R2.1, R3.1, R108.1, U5.3
unnamed: R108.2, SW1.4
TAG_3V3: J2.6, J101.5, SW1.10, SW1.11, SW1.12
TAG_3V3_EN: U4.6, U6.12 (PA6)
TAG_3V3_IN: J1.2, U4.1
TAG_MIRROR: J1.1, U6.10 (PA4)
TAG_RESET: J2.3, J101.1, R104.1
TAG_SCK: J2.4, J101.4, U6.7 (PA1)
TAG_SWDIO: J2.2, J101.3, U2.1
TAG_VBAT: J2.5, J101.6, SW1.7, SW1.8, SW1.9, U3.4
VBAT_ADC: U3.1, U6.8 (PA2)
VUSB: D1.2 (A), D105.2 (A), J104.1 (VBUS)
~TAG_VBAT_EN: U5.6, U6.13 (PA7)

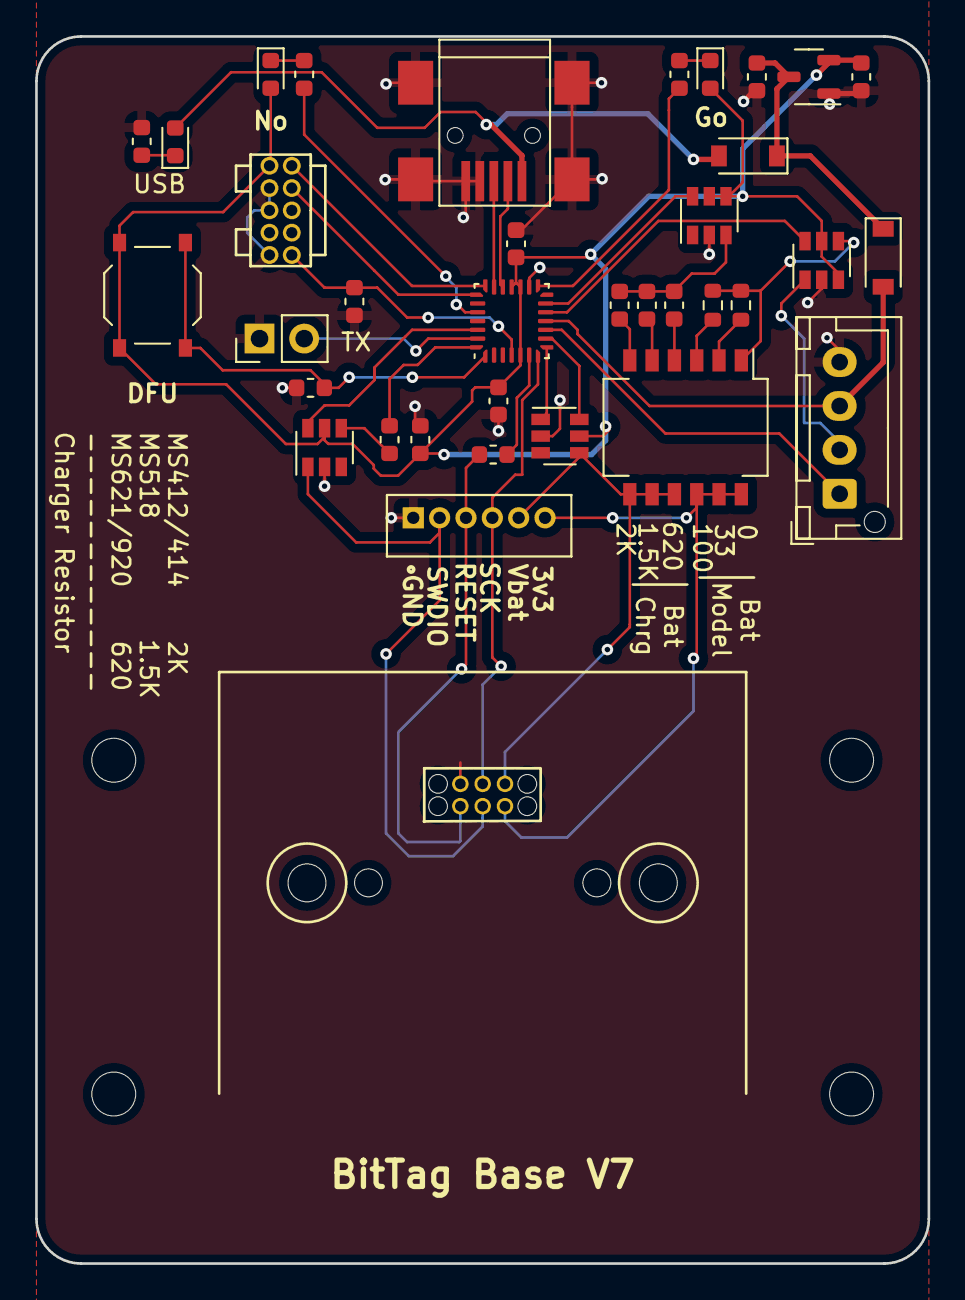
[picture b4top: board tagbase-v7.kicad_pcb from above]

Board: 2 copper layers, 50.8 x 69.9 mm, 40 parts (0 on the bottom side), 39 nets.

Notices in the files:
parts and their libraries:
Copyright 2016 Accelerated Designs. All rights reserved.
